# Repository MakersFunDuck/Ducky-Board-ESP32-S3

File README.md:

# Ducky Board - Esp32-S3

This project is a custom-designed breakout board for the ESP32-S3 chip, created using KiCad 9. The board features native USB-C programming support, and includes an integrated Li-Ion battery charger,

## Hardware

- **Features**

-ESP32-S3 Microcontroller

-USB-C Port

  Used for both power input and firmware flashing

-Li-Ion Battery Charging Circuit

  Integrated charger IC with status indicators

  Supports single-cell Li-Ion/LiPo batteries

-Compact Breakout Form Factor

  All key GPIOs broken out

## Design Details

-Designed entirely in KiCad 9

-Includes schematics, PCB layout files, and Gerber files

-Part selection is optimized for manufacturing and re-usability for DIY projects

## License

See the [LICENSE](LICENSE) file for details.

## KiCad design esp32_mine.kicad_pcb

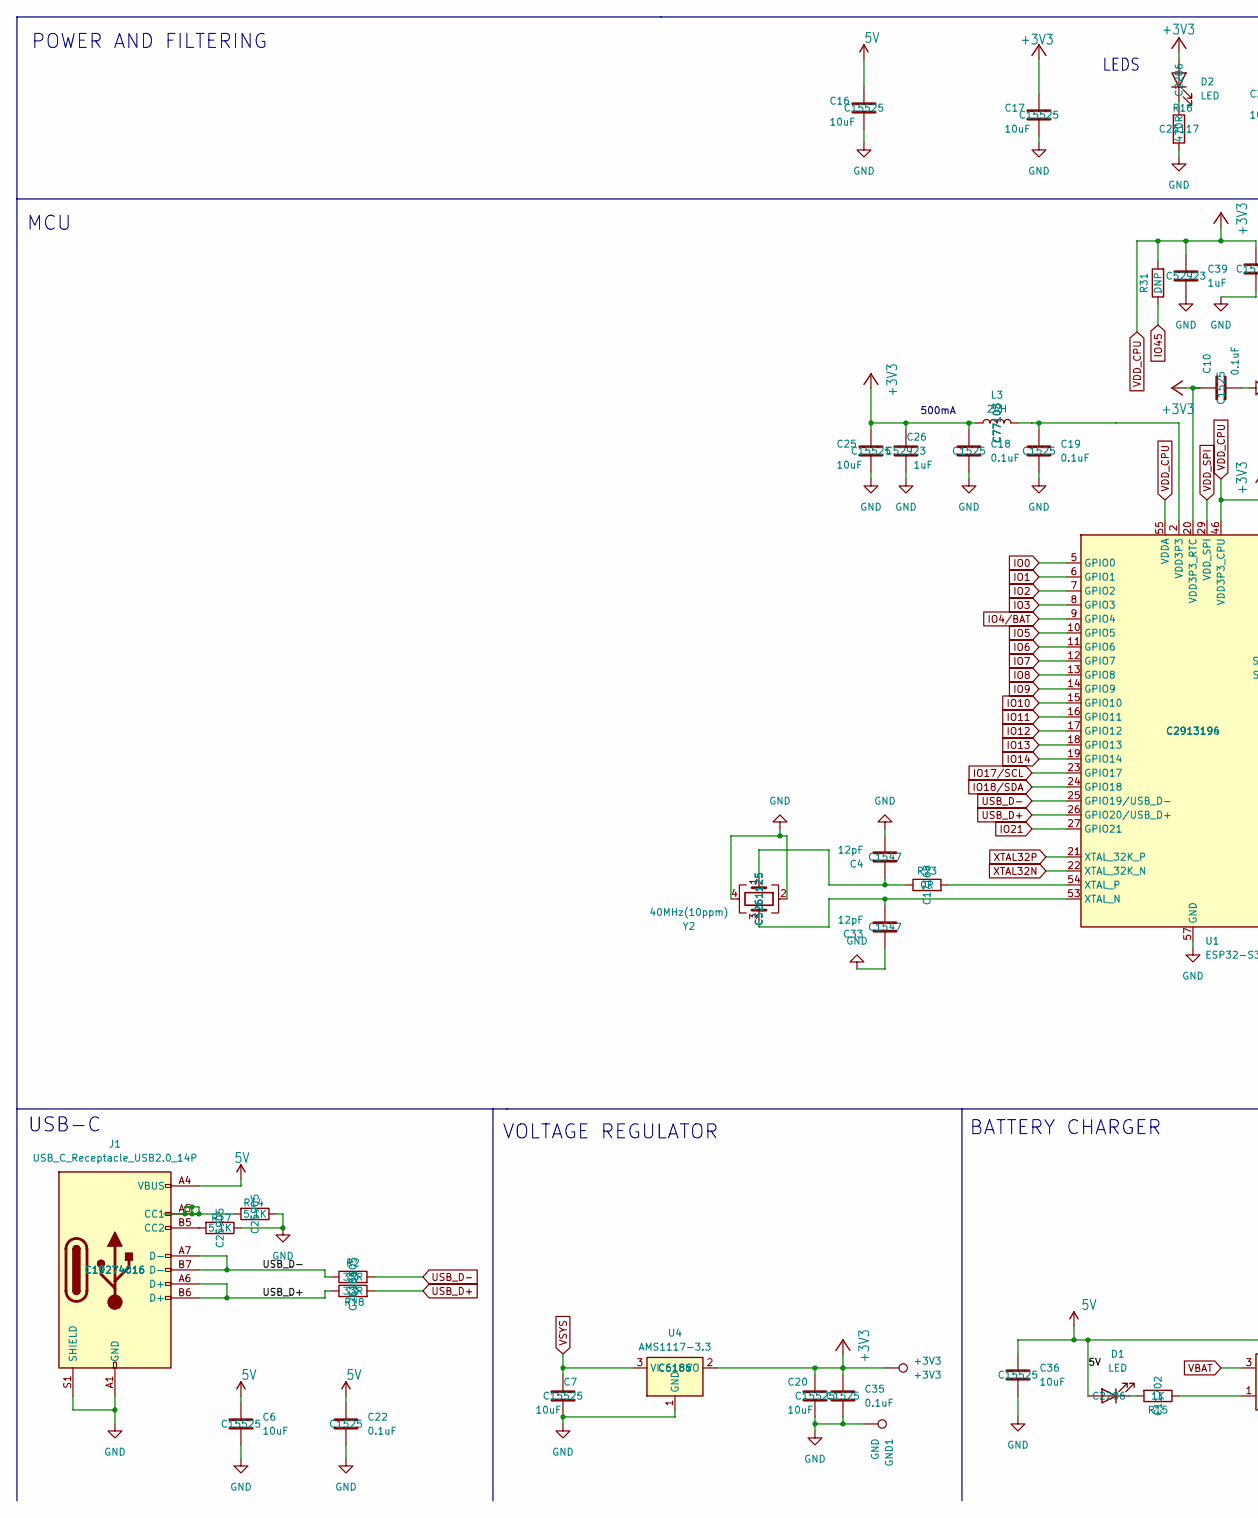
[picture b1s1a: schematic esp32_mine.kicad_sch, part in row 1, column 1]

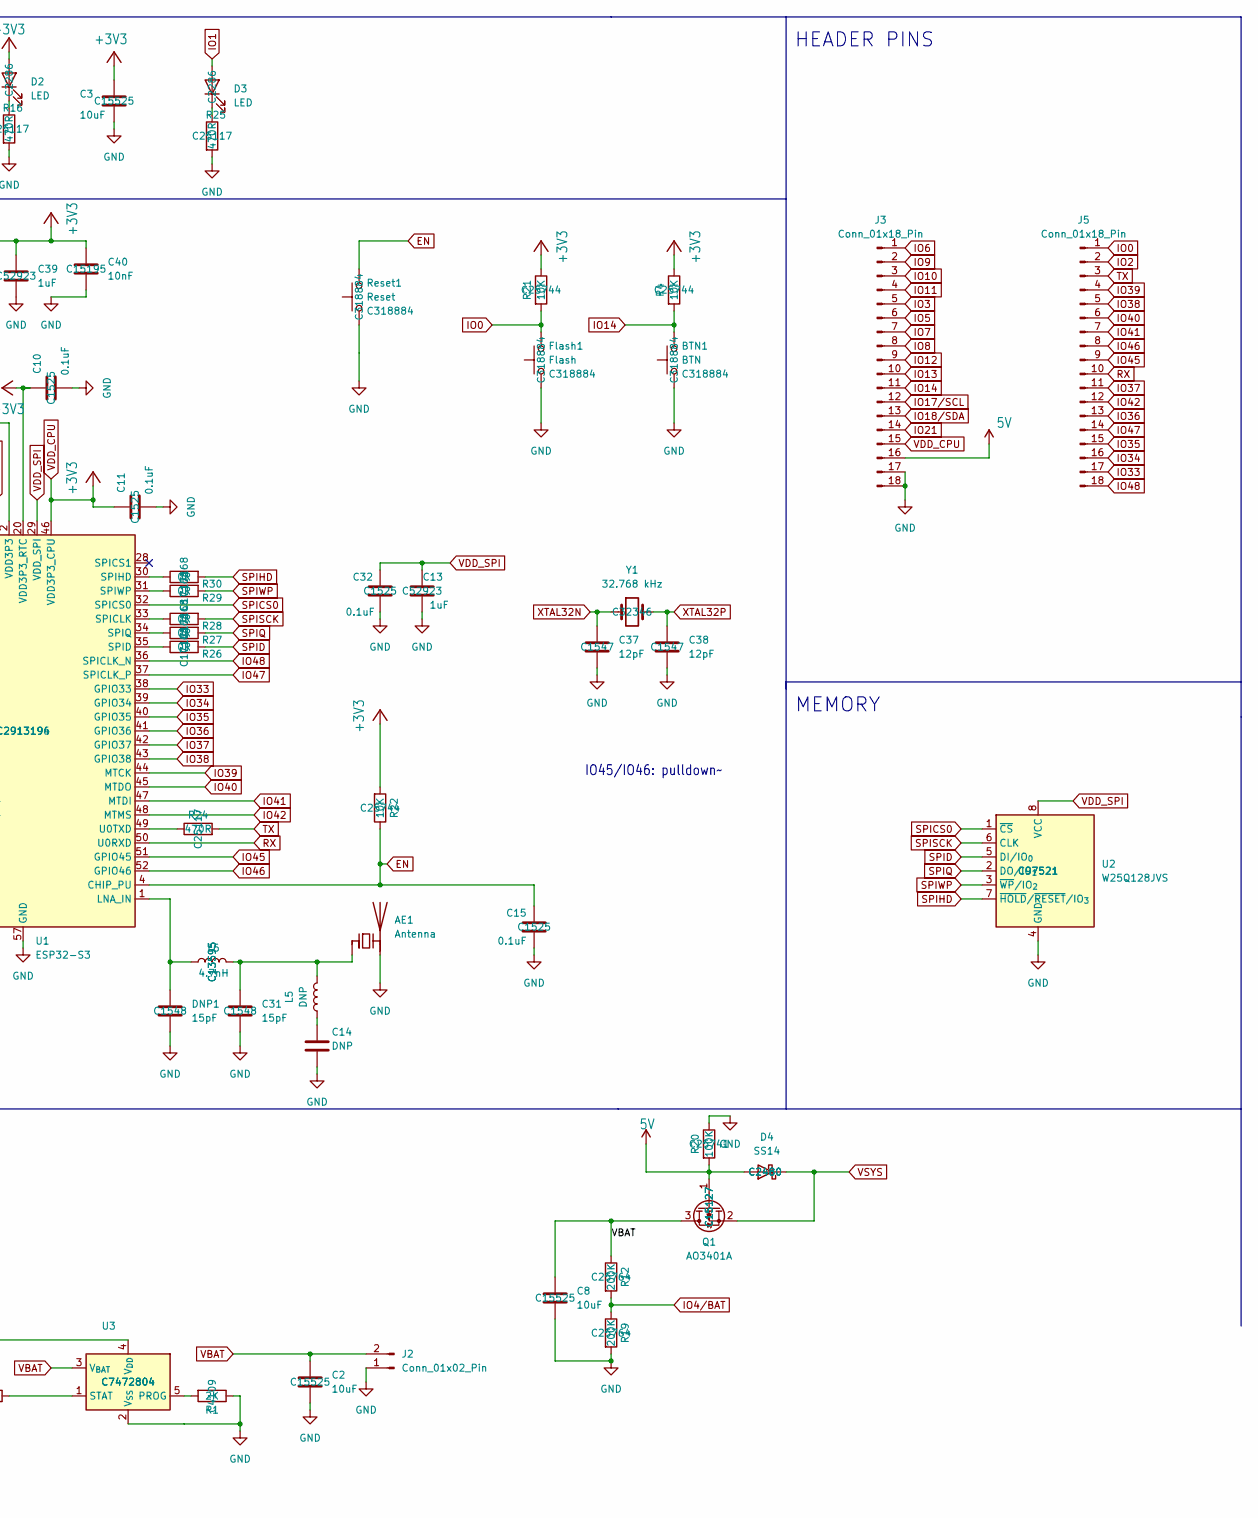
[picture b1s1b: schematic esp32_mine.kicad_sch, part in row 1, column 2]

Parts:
+3V3: +3V3; TestPoint_Pad_D1.0mm
AE1: Antenna; Texas_SWRA117D_2.4GHz_Left
BTN1: BTN; SW_Push_1P1T_XKB_TS-1187A; MNF PART NUMBER C318884; LCSC C318884
C2, C3, C6, C7, C8, C16, C17, C20, C25, C36: 10uF; C_0402_1005Metric; MNF PART NUMBER C15525; LCSC C15525
C4, C33, C37, C38: 12pF; C_0402_1005Metric; MNF PART NUMBER C1547; LCSC C1547
C10, C11, C15, C18, C19, C22, C32, C35: 0.1uF; C_0402_1005Metric; MNF PART NUMBER C1525; LCSC C1525
C13, C26, C39: 1uF; C_0402_1005Metric; MNF PART NUMBER C52923; LCSC C52923
C14: DNP; C_0402_1005Metric
C31: 15pF; C_0402_1005Metric; MNF PART NUMBER C1548; LCSC C1548
C40: 10nF; C_0402_1005Metric; MNF PART NUMBER C15195; LCSC C15195
D1, D2, D3: LED; LED_0603_1608Metric; MNF PART NUMBER C2286; LCSC C2286
D4: SS14; D_SMA; MNF PART NUMBER C2480; LCSC C2480
DNP1: 15pF; C_0402_1005Metric; MNF PART NUMBER C1548; LCSC C1548
Flash1: Flash; SW_Push_1P1T_XKB_TS-1187A; MNF PART NUMBER C318884; LCSC C318884
GND1: GND; TestPoint_Pad_D1.0mm
J1: USB_C_Receptacle_USB2.0_14P; USB_C_Receptacle_HCTL_HC-TYPE-C-16P-01A; MNF PART NUMBER C19274016; LCSC C19274016
J2: Conn_01x02_Pin; PinSocket_1x02_P2.54mm_Vertical
J3, J5: Conn_01x18_Pin; PinHeader_1x18_P2.54mm_Vertical
L3: 2nH; L_0402_1005Metric; MNF PART NUMBER C77103; LCSC C77103
L5: DNP; L_0402_1005Metric
L6: 4.7nH; L_0402_1005Metric; MNF PART NUMBER C13595; LCSC C13595
Q1: AO3401A; SOT-23; MNF PART NUMBER C15127; LCSC C15127
R1: 2K; R_0402_1005Metric; MNF PART NUMBER C4109; LCSC C4109
R2, R18: 33R; R_0402_1005Metric; MNF PART NUMBER C25105; LCSC C25105
R4, R21, R22: 10K; R_0402_1005Metric; MNF PART NUMBER C25744; LCSC C25744
R12, R19: 200K; R_0402_1005Metric; MNF PART NUMBER C25764; LCSC C25764
R14, R17: 5.1K; R_0402_1005Metric; MNF PART NUMBER C25905; LCSC C25905
R15: 1K; R_0402_1005Metric; MNF PART NUMBER C11702; LCSC C11702
R16, R24, R25: 470R; R_0402_1005Metric; MNF PART NUMBER C25117; LCSC C25117
R20: 100K; R_0402_1005Metric; MNF PART NUMBER C25741; LCSC C25741
R23, R26, R27, R28, R29, R30: 0R; R_0402_1005Metric; MNF PART NUMBER C17168; LCSC C17168
R31: DNP; R_0402_1005Metric
Reset1: Reset; SW_Push_1P1T_XKB_TS-1187A; MNF PART NUMBER C318884; LCSC C318884
U1: ESP32-S3; QFN-56-1EP_7x7mm_P0.4mm_EP4x4mm; MNF PART NUMBER C2913196; LCSC C2913194
U2: W25Q128JVS; SOIC-8_5.3x5.3mm_P1.27mm; MNF PART NUMBER C97521; LCSC C97521
U3: MCP73831-2-OT; SOT-23-5; MNF PART NUMBER C7472804; LCSC C7472804
U4: AMS1117-3.3; SOT-223-3_TabPin2; MNF PART NUMBER C6186; LCSC C6186
Y1: 32.768 kHz; Crystal_SMD_3215-2Pin_3.2x1.5mm; MNF PART NUMBER C32346; LCSC C32346
Y2: 40MHz(10ppm); Crystal_SMD_2520-4Pin_2.5x2.0mm; MNF PART NUMBER C5261125; LCSC C5261125

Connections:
5V: C6.1, C16.1, C22.1, C36.1, D1.2 (A), D4.2 (A), J1.A4 (VBUS), J1.A9 (VBUS), J1.B4 (VBUS), J1.B9 (VBUS), J3.16, Q1.1 (G), R20.2, U3.4 (V_{DD})
EN: C15.1, R22.1, Reset1.2, U1.4 (CHIP_PU)
GND: AE1.2 (PCB_Trace), BTN1.1, C2.2, C3.2, C4.2, C6.2, C7.2, C8.2, C10.2, C11.2, C13.2, C14.2, C15.2, C16.2, C17.2, C18.2, C19.2, C20.2, C22.2, C25.2, C26.2, C31.2, C32.2, C33.1, C35.2, C36.2, C37.2, C38.2, C39.2, C40.2, DNP1.2, Flash1.1, GND1.1, J1.A1 (GND), J1.A12 (GND), J1.B1 (GND), J1.B12 (GND), J1.S1 (SHIELD), J2.1, J3.17, J3.18, R1.1, R14.1, R16.2, R17.1, R19.2, R20.1, R25.2, Reset1.1, U1.57 (GND), U2.4 (GND), U3.2 (V_{SS}), U4.1 (GND), Y2.2, Y2.4
IO0: Flash1.2, J5.1, R21.2, U1.5 (GPIO0)
IO1: D3.2 (A), U1.6 (GPIO1)
IO2: J5.2, U1.7 (GPIO2)
IO3: J3.5, U1.8 (GPIO3)
IO4/BAT: R12.2, R19.1, U1.9 (GPIO4)
IO5: J3.6, U1.10 (GPIO5)
IO6: J3.1, U1.11 (GPIO6)
IO7: J3.7, U1.12 (GPIO7)
IO8: J3.8, U1.13 (GPIO8)
IO9: J3.2, U1.14 (GPIO9)
IO10: J3.3, U1.15 (GPIO10)
IO11: J3.4, U1.16 (GPIO11)
IO12: J3.9, U1.17 (GPIO12)
IO13: J3.10, U1.18 (GPIO13)
IO14: BTN1.2, J3.11, R4.2, U1.19 (GPIO14)
IO17/SCL: J3.12, U1.23 (GPIO17)
IO18/SDA: J3.13, U1.24 (GPIO18)
IO21: J3.14, U1.27 (GPIO21)
IO33: J5.17, U1.38 (GPIO33)
IO34: J5.16, U1.39 (GPIO34)
IO35: J5.15, U1.40 (GPIO35)
IO36: J5.13, U1.41 (GPIO36)
IO37: J5.11, U1.42 (GPIO37)
IO38: J5.5, U1.43 (GPIO38)
IO39: J5.4, U1.44 (MTCK)
IO40: J5.6, U1.45 (MTDO)
IO41: J5.7, U1.47 (MTDI)
IO42: J5.12, U1.48 (MTMS)
IO45: J5.9, R31.1, U1.51 (GPIO45)
IO46: J5.8, U1.52 (GPIO46)
IO47: J5.14, U1.37 (SPICLK_P)
IO48: J5.18, U1.36 (SPICLK_N)
unnamed: AE1.1 (FEED), C31.1, L5.2, L6.2
unnamed: C4.1, R23.1, Y2.1
unnamed: C14.1, L5.1
unnamed: C19.1, L3.2, U1.2 (VDD3P3), U1.3 (VDD3P3)
unnamed: D1.1 (K), R15.2
unnamed: D2.1 (K), R16.1
unnamed: D3.1 (K), R25.1
unnamed: J1.A5 (CC1), R14.2
unnamed: J1.B5 (CC2), R17.2
unnamed: DNP1.1, L6.1, U1.1 (LNA_IN)
unnamed: R28.1, U1.33 (SPICLK)
unnamed: R26.1, U1.35 (SPID)
unnamed: R30.1, U1.30 (SPIHD)
unnamed: R27.1, U1.34 (SPIQ)
unnamed: R29.1, U1.31 (SPIWP)
unnamed: R24.1, U1.49 (U0TXD)
unnamed: C33.2, U1.53 (XTAL_N), Y2.3
unnamed: R23.2, U1.54 (XTAL_P)
unnamed: R1.2, U3.5 (PROG)
unnamed: R15.1, U3.1 (STAT)
RX: J5.10, U1.50 (U0RXD)
SPICS0: U1.32 (SPICS0), U2.1 (~CS)
SPID: R26.2, U2.5 (DI/IO_{0})
SPIHD: R30.2, U2.7 (~HOLD/~RESET/IO_{3})
SPIQ: R27.2, U2.2 (DO/IO_{1})
SPISCK: R28.2, U2.6 (CLK)
SPIWP: R29.2, U2.3 (~WP/IO_{2})
TX: J5.3, R24.2
USB_D+: J1.A6 (D+), J1.B6 (D+), R18.1, R18.2, U1.26 (GPIO20/USB_D+)
USB_D-: J1.A7 (D-), J1.B7 (D-), R2.1, R2.2, U1.25 (GPIO19/USB_D-)
VBAT: C2.1, C8.1, J2.2, Q1.3 (D), R12.1, U3.3 (V_{BAT})
VDD_CPU: +3V3.1, C3.1, C10.1, C11.1, C17.1, C18.1, C20.1, C25.1, C26.1, C35.1, C39.1, C40.1, D2.2 (A), J3.15, L3.1, R4.1, R21.1, R22.2, R31.2, U1.20 (VDD3P3_RTC), U1.46 (VDD3P3_CPU), U1.55 (VDDA), U1.56 (VDDA), U4.2 (VO)
VDD_SPI: C13.1, C32.1, U1.29 (VDD_SPI), U2.8 (VCC)
VSYS: C7.1, D4.1 (K), Q1.2 (S), U4.3 (VI)
XTAL32N: C37.1, U1.22 (XTAL_32K_N), Y1.1
XTAL32P: C38.1, U1.21 (XTAL_32K_P), Y1.2

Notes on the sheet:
BATTERY CHARGER
VOLTAGE REGULATOR
500mA
LEDS
MCU
HEADER PINS
MEMORY
POWER AND FILTERING
IO45/IO46: pulldown~~{}
USB-C

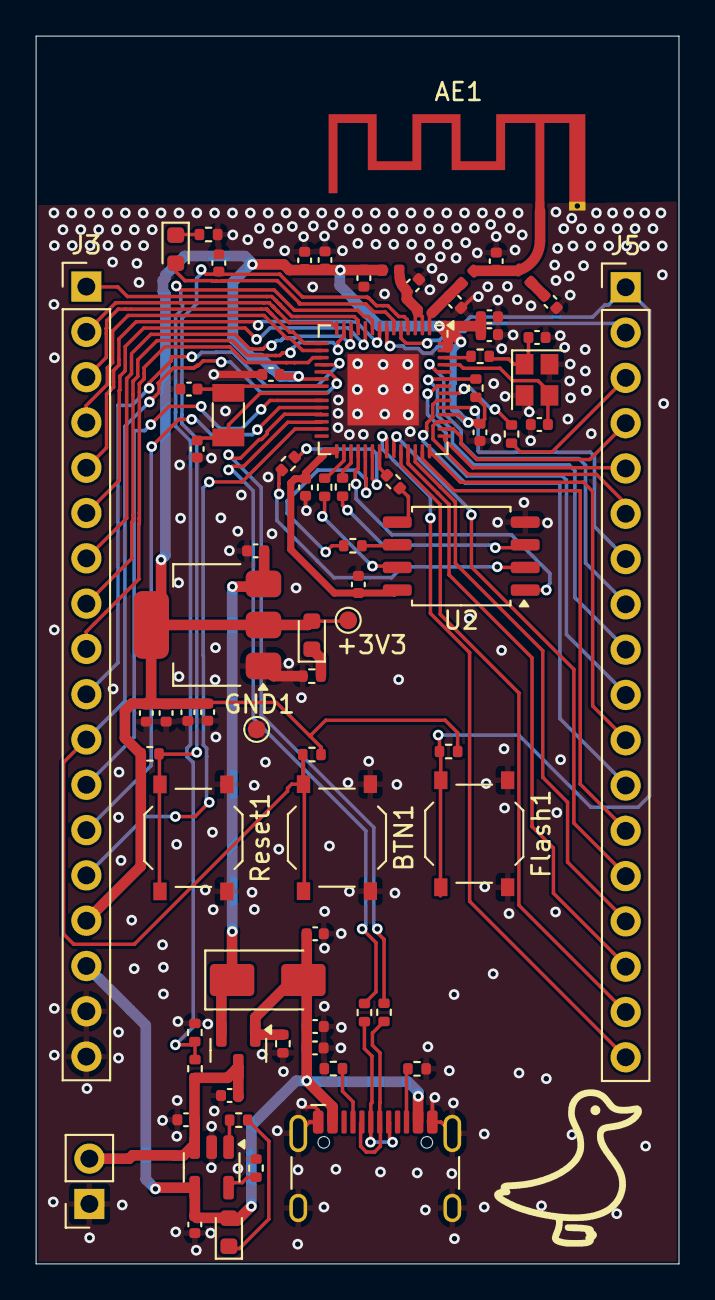
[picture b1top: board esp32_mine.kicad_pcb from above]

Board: 2 copper layers, 36.0 x 68.8 mm, 75 parts (0 on the bottom side), 71 nets.

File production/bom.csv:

Designator,Footprint,Quantity,Value,LCSC Part #
+3V3,TestPoint_Pad_D1.0mm,1,+3V3,
AE1,Texas_SWRA117D_2.4GHz_Left,1,Antenna,
BTN1,SW_Push_1P1T_XKB_TS-1187A,1,BTN,
"C10, C11, C15, C18, C19, C22, C32, C35",0402,8,0.1uF,
"C13, C26, C39",0402,3,1uF,
"C16, C17, C2, C20, C25, C3, C36, C6, C7, C8",0402,10,10uF,
"C31, DNP1",0402,2,15pF,
"C33, C37, C38, C4",0402,4,12pF,
C40,0402,1,10nF,
"D1, D2, D3",0603,3,LED,
D4,D_SMA,1,SS14,
FLASH1,SW_Push_1P1T_XKB_TS-1187A,1,Flash,
GND1,TestPoint_Pad_D1.0mm,1,GND,
J1,USB_C_Receptacle_HCTL_HC-TYPE-C-16P-01A,1,USB_C_Receptacle_USB2.0_14P,
J2,PinSocket_1x02_P2.54mm_Vertical,1,Conn_01x02_Pin,
"J3, J5",PinHeader_1x18_P2.54mm_Vertical,2,Conn_01x18_Pin,
L3,0402,1,2nH,
L6,0402,1,4.7nH,
Q1,SOT-23,1,AO3401A,
R1,0402,1,2K,
"R12, R19",0402,2,200K,
"R14, R17",0402,2,5.1K,
R15,0402,1,1K,
"R16, R24, R25",0402,3,470R,
"R18, R2",0402,2,33R,
R20,0402,1,100K,
"R21, R22, R4",0402,3,10K,
"R23, R26, R27, R28, R29, R30",0402,6,0R,
RESET1,SW_Push_1P1T_XKB_TS-1187A,1,Reset,
U1,QFN-56-1EP_7x7mm_P0.4mm_EP4x4mm,1,ESP32-S3,
U2,SOIC-8_5.3x5.3mm_P1.27mm,1,W25Q128JVS,
U3,SOT-23-5,1,MCP73831-2-OT,
U4,SOT-223-3_TabPin2,1,AMS1117-3.3,
Y1,Crystal_SMD_3215-2Pin_3.2x1.5mm,1,32.768 kHz,
Y2,Crystal_SMD_2520-4Pin_2.5x2.0mm,1,40MHz(10ppm),

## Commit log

2025-05-03 readme updated
2025-05-08 PDF files for schematics and layout added
2025-06-15 remove kicad lock files
